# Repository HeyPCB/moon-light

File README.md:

# Luna, the night-light moon

**A sleepy moon that turns on at dusk and tucks itself in after you fall asleep.**

Luna is a crescent-moon night light on USB-C. An APDS-9306 ambient light sensor tells a CH32V003 when the room has gone dark; eight orange LEDs along the moon's inner curve then fade up to a candle-coloured glow, and fade out again after a 15, 45 or 90 minute sleep timer. It stays off until the room sees daylight. Pat its gold cheek to switch it by hand; hang it on a nail by its keyhole.

| Layers | Size | Parts | Nets | Connections routed | Vias | ERC errors | DRC errors / unconnected / parity | BOM @100 |
|---|---|---|---|---|---|---|---|---|
| 2 | 54.0 x 62.7 mm | 32 (+4 pads) | 22 | 67 -> 0 open | 13 | 0 | 0 / 0 / 0 | $1.43 |

**Not fabricated, assembled or powered yet.** Every number on this page is measured by KiCad 10.0.6 on
the files in this repository ([`report.json`](report.json), [`measured.json`](measured.json)) or read
from the live JLC/LCSC catalogue ([`bom_cost.json`](bom_cost.json)).

| | |
|---|---|
| Spec, power budget, BOM | [`SPEC.md`](SPEC.md) |
| Store copy | [`STORE_COPY.md`](STORE_COPY.md) |
| KiCad 10 project | [`kicad/`](kicad/) |
| Gerbers, drill, BOM, CPL, STEP, schematic PDF | [`fab/`](fab/) |
| Firmware | [`firmware/`](firmware/) |
| Renders | [front](media/top.png), [back](media/bottom.png), [hero](media/hero.png), [Circuit World thumbnail](media/circuit-world.png) |
| Brief and generator | [`design/`](design/) |

## What's on it

- **Glow:** 8 XL-1608UOC orange (605 nm) LEDs, each with its own 220 Ohm from 5 V, switched together by an AO3400A on TIM1 CH4 at 1 kHz.
- **Light sensor:** Broadcom APDS-9306-065 at I2C 0x52, 3.3 V, bit-banged I2C with 10k pull-ups.
- **MCU:** CH32V003F4P6 at 3.3 V from an XC6206 LDO (JLC Basic).
- **Touch:** a 4 mm ENIG cheek pad through 1 kOhm, read by ch32fun's ADC touch.
- **Mounting:** a keyhole cutout near the centre of mass; USB-C out of the bottom.
- **Power:** USB-C, about 0.2 W while glowing (SPEC.md).

## Finish

Blue solder mask, White silkscreen, ENIG copper finish, 1.6 mm FR4, top-side SMT assembly (J1: an SMD part whose shell legs go through plated holes, soldered on the same SMT line).
The gold art is bare copper under a mask opening (ENIG), drawn with its own keep-out so no track runs
under it. The QR code on the back opens [https://heypcb.ai/world/b/e2974968006f](https://heypcb.ai/world/b/e2974968006f).

## How it was made

Designed with the HeyPCB method on KiCad 10.0.6, headless, by the `heypcb-kicad` pipeline: a written
brief composed from reusable circuit blocks, every pin from KiCad's own symbol library, every part bound
to an LCSC number from a dated catalogue read, then ERC, a netlist round trip, locked placement,
Freerouting 2.4.1, pours, silkscreen and board art, DRC with schematic parity, DFM and a fab gate,
each stage gated by a measurement. `design/make_brief.py` regenerates the brief (outline, part
locks and art) from code.

Part of the [heypcb.ai merch collection](https://github.com/HeyPCB/merch).

## License

Hardware: [CERN-OHL-S v2](LICENSE). Firmware: MIT (see [`firmware/LICENSE`](firmware/LICENSE)). KiCad's symbol, footprint and 3D
libraries used in the design are CC-BY-SA 4.0 with the KiCad library exception.

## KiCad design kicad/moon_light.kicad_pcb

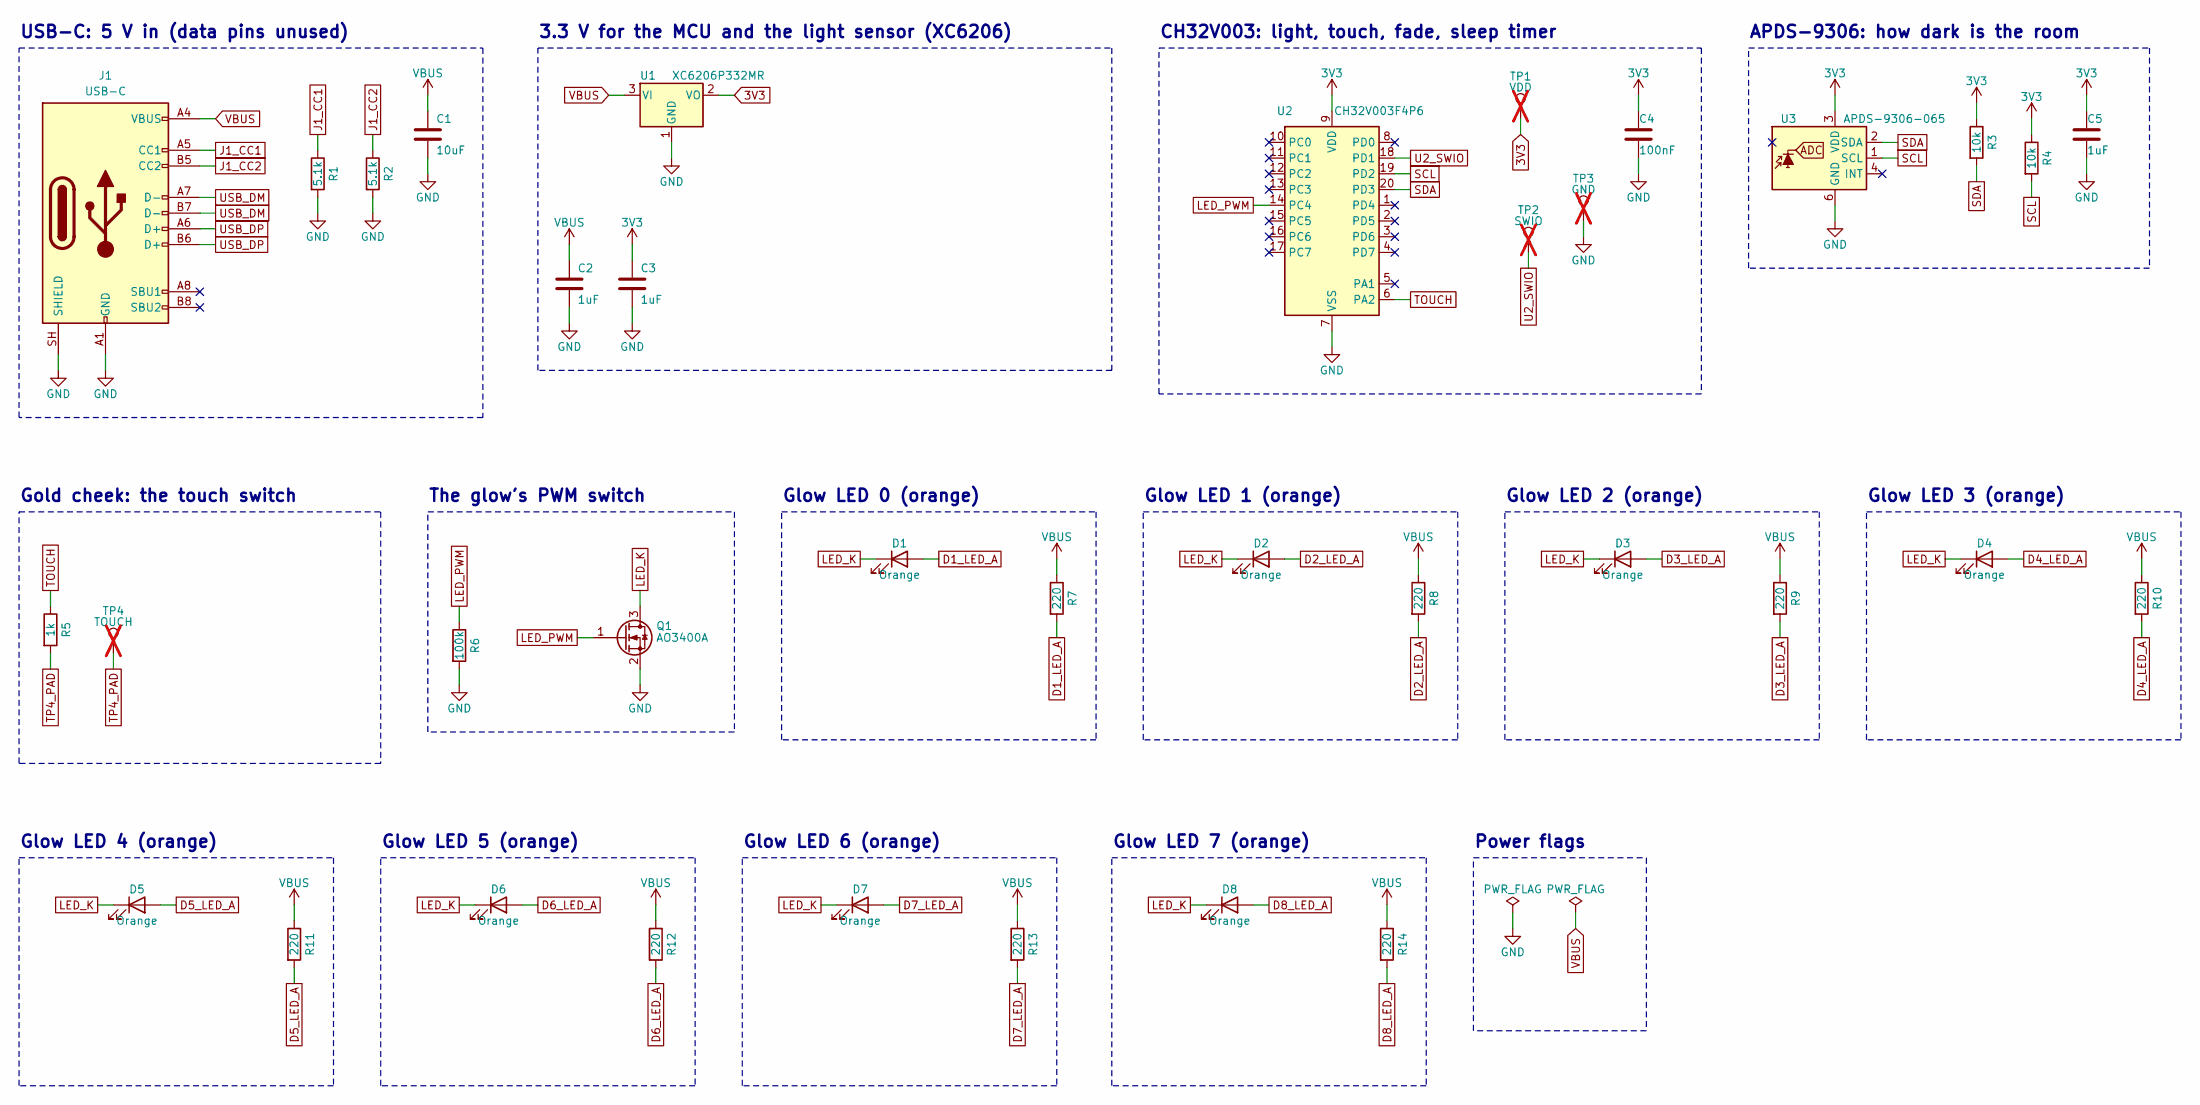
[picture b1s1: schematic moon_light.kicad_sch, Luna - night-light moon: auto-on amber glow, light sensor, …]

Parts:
C1: 10uF; C_0805_2012Metric; MPN CL21A106KAYNNNE; LCSC C15850
C2, C3: 1uF; C_0603_1608Metric; MPN CL10A105KB8NNNC; LCSC C15849
C4: 100nF; C_0603_1608Metric; MPN CC0603KRX7R9BB104; LCSC C14663
C5: 1uF; C_0402_1005Metric; MPN CL05A105KA5NQNC; LCSC C52923
D1, D2, D3, D4, D5, D6, D7, D8: Orange; LED_0603_1608Metric; MPN XL-1608UOC-06; LCSC C965800
J1: USB-C; USB_C_Receptacle_HRO_TYPE-C-31-M-12; MPN TYPE-C-31-M-12; LCSC C165948
Q1: AO3400A; SOT-23; MPN AO3400A; LCSC C20917
R1, R2: 5.1k; R_0402_1005Metric; MPN 0402WGF5101TCE; LCSC C25905
R3, R4: 10k; R_0402_1005Metric; MPN 0402WGF1002TCE; LCSC C25744
R5: 1k; R_0603_1608Metric; MPN 0603WAF1001T5E; LCSC C21190
R6: 100k; R_0603_1608Metric; MPN 0603WAF1003T5E; LCSC C25803
R7, R8, R9, R10, R11, R12, R13, R14: 220; R_0603_1608Metric; MPN 0603WAF2200T5E; LCSC C22962
TP1: VDD; TestPoint_Pad_1.0x1.0mm; not fitted
TP2: SWIO; TestPoint_Pad_1.0x1.0mm; not fitted
TP3: GND; TestPoint_Pad_1.0x1.0mm; not fitted
TP4: TOUCH; TestPoint_Pad_D4.0mm; not fitted
U1: XC6206P332MR; SOT-23-3; MPN XC6206P332MR-G; LCSC C5446
U2: CH32V003F4P6; TSSOP-20_4.4x6.5mm_P0.65mm; MPN CH32V003F4P6; LCSC C5187096
U3: APDS-9306-065; Broadcom_DFN-6_2x2mm_P0.65mm; MPN APDS-9306-065; LCSC C2649498

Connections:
3V3: C3.1, C4.1, C5.1, R3.1, R4.1, TP1.1, U1.2 (VO), U2.9 (VDD), U3.3 (VDD)
D1_LED_A: D1.2 (A), R7.2
D2_LED_A: D2.2 (A), R8.2
D3_LED_A: D3.2 (A), R9.2
D4_LED_A: D4.2 (A), R10.2
D5_LED_A: D5.2 (A), R11.2
D6_LED_A: D6.2 (A), R12.2
D7_LED_A: D7.2 (A), R13.2
D8_LED_A: D8.2 (A), R14.2
GND: C1.2, C2.2, C3.2, C4.2, C5.2, J1.A1 (GND), J1.A12 (GND), J1.B1 (GND), J1.B12 (GND), J1.SH (SHIELD), Q1.2 (S), R1.2, R2.2, R6.2, TP3.1, U1.1 (GND), U2.7 (VSS), U3.6 (GND)
J1_CC1: J1.A5 (CC1), R1.1
J1_CC2: J1.B5 (CC2), R2.1
LED_K: D1.1 (K), D2.1 (K), D3.1 (K), D4.1 (K), D5.1 (K), D6.1 (K), D7.1 (K), D8.1 (K), Q1.3 (D)
LED_PWM: Q1.1 (G), R6.1, U2.14 (PC4)
SCL: R4.2, U2.19 (PD2), U3.1 (SCL)
SDA: R3.2, U2.20 (PD3), U3.2 (SDA)
TOUCH: R5.1, U2.6 (PA2)
TP4_PAD: R5.2, TP4.1
U2_SWIO: TP2.1, U2.18 (PD1)
USB_DM: J1.A7 (D-), J1.B7 (D-)
USB_DP: J1.A6 (D+), J1.B6 (D+)
VBUS: C1.1, C2.1, J1.A4 (VBUS), J1.A9 (VBUS), J1.B4 (VBUS), J1.B9 (VBUS), R7.1, R8.1, R9.1, R10.1, R11.1, R12.1, R13.1, R14.1, U1.3 (VI)

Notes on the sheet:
USB-C: 5 V in (data pins unused)
3.3 V for the MCU and the light sensor (XC6206)
CH32V003: light, touch, fade, sleep timer
APDS-9306: how dark is the room
Gold cheek: the touch switch
The glow's PWM switch
Glow LED 0 (orange)
Glow LED 1 (orange)
Glow LED 2 (orange)
Glow LED 3 (orange)
Glow LED 4 (orange)
Glow LED 5 (orange)
Glow LED 6 (orange)
Glow LED 7 (orange)
Power flags

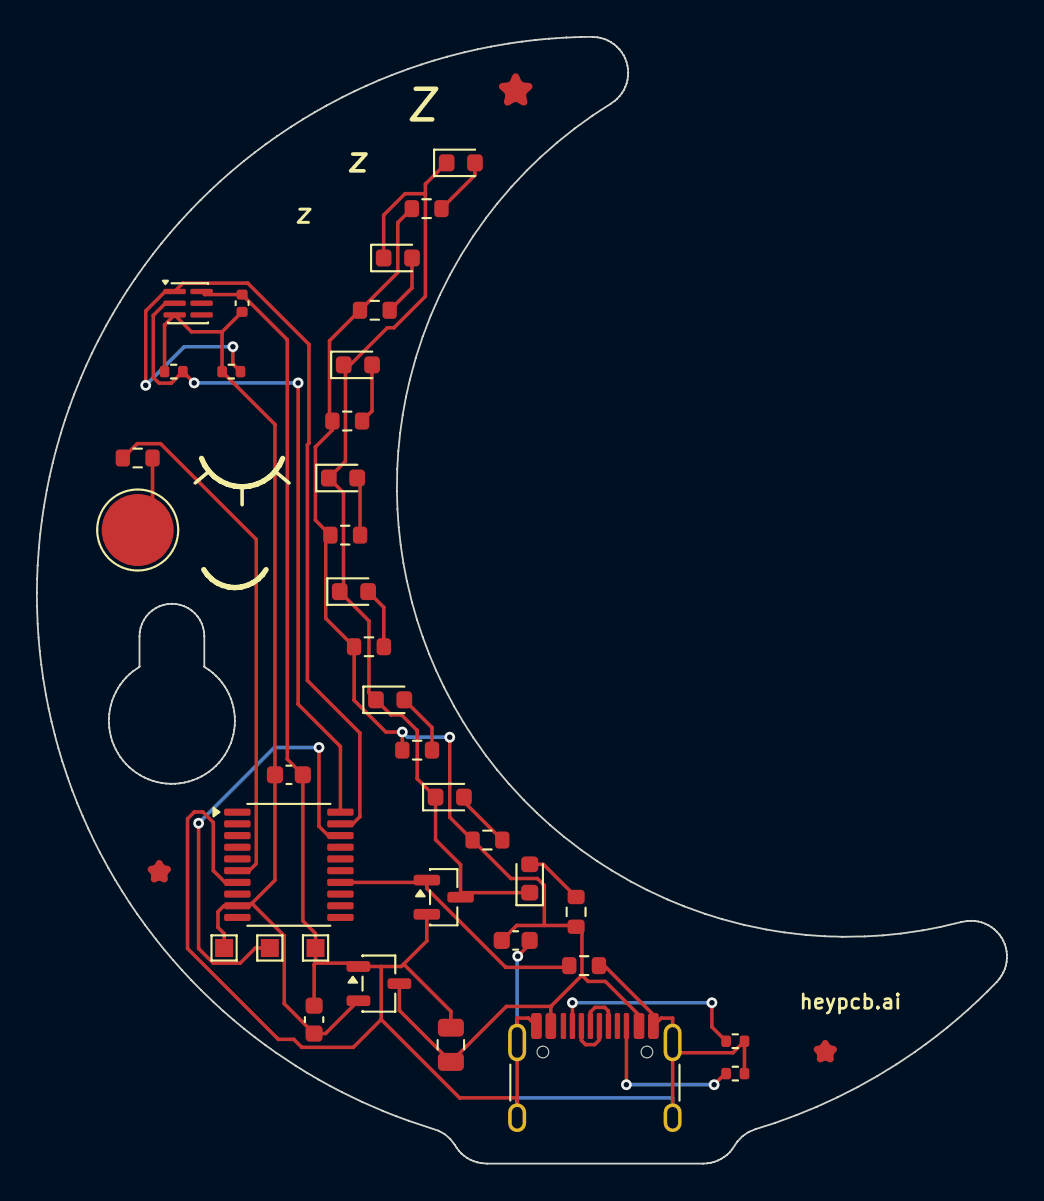
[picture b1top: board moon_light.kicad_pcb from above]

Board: 2 copper layers, 53.9 x 62.6 mm, 36 parts (0 on the bottom side), 22 nets.

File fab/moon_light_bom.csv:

"Reference","Value","Footprint","MPN","LCSC","Qty"
"C1","10uF","Capacitor_SMD:C_0805_2012Metric","CL21A106KAYNNNE","C15850","1"
"C2,C3","1uF","Capacitor_SMD:C_0603_1608Metric","CL10A105KB8NNNC","C15849","2"
"C4","100nF","Capacitor_SMD:C_0603_1608Metric","CC0603KRX7R9BB104","C14663","1"
"C5","1uF","Capacitor_SMD:C_0402_1005Metric","CL05A105KA5NQNC","C52923","1"
"D1,D2,D3,D4,D5,D6,D7,D8","Orange","LED_SMD:LED_0603_1608Metric","XL-1608UOC-06","C965800","8"
"J1","USB-C","Connector_USB:USB_C_Receptacle_HRO_TYPE-C-31-M-12","TYPE-C-31-M-12","C165948","1"
"Q1","AO3400A","Package_TO_SOT_SMD:SOT-23","AO3400A","C20917","1"
"R1,R2","5.1k","Resistor_SMD:R_0402_1005Metric","0402WGF5101TCE","C25905","2"
"R3,R4","10k","Resistor_SMD:R_0402_1005Metric","0402WGF1002TCE","C25744","2"
"R5","1k","Resistor_SMD:R_0603_1608Metric","0603WAF1001T5E","C21190","1"
"R6","100k","Resistor_SMD:R_0603_1608Metric","0603WAF1003T5E","C25803","1"
"R7,R8,R9,R10,R11,R12,R13,R14","220","Resistor_SMD:R_0603_1608Metric","0603WAF2200T5E","C22962","8"
"U1","XC6206P332MR","Package_TO_SOT_SMD:SOT-23-3","XC6206P332MR-G","C5446","1"
"U2","CH32V003F4P6","Package_SO:TSSOP-20_4.4x6.5mm_P0.65mm","CH32V003F4P6","C5187096","1"
"U3","APDS-9306-065","OptoDevice:Broadcom_DFN-6_2x2mm_P0.65mm","APDS-9306-065","C2649498","1"
